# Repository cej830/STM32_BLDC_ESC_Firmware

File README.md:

# STM32 Sensorless BLDC ESC

STM32F103C8 기반 센서리스 BLDC ESC. 회로·4-layer PCB 설계 및 펌웨어 구현을 수행하고
12V에서 A2212/13T 1000kV 모터의 무부하 구동을 확인했다.

## Highlights
- 4층 기판 3상 ESC 하드웨어 설계부터 회로도 작성, 조립 및 보드 브링업 수행
- 오픈루프 기동 및 BEMF(역기전력) 클로즈드 루프 정류를 적용한 센서리스 6스텝 제어 구현
- ADC 기반 제로 크로싱 검출 방식 적용, 고듀티 구간에서는 외부 비교기 및 TIM2 Input Capture 로 전환
- 12V 환경에서 A2212/13T 1000kV 모터를 무부하 조건에서 CCR 1750/1800까지 구동 시험 완료

## Hardware

- **MCU:** STM32F103C8T6
- **Gate driver / MOSFET:** DRV8300 / IRFH7440 × 6
- **PCB:** 4-layer, 1.6mm
- **Power:** 12V→5V Buck, USB 5V와 diode ORing, 3.3V LDO
- **BEMF sensing:** 상전압 ADC 입력 및 TLV3202 외부 비교기
- **Current sensing:** 10mΩ 로우사이드 션트 및 INA180A3 × 3
- **Interface:** USB 2.0 FullSpeed, UART, LED, 버튼, 가변저항, 테스트 포인트

회로,BOM 작성, PCB 부품 배치 및 배선, 보드 bring-up을 직접 수행했다. 부품 실장은 SMT 조립을 외주하였다.

### 3D Board View

### Schematic

### PCB Layout — Front / Back

### Assembled Board

실물 수정: USB 풀업 저항 직결, Vcom 비교기 입력 커패시터 제거.

[하드웨어 구성 상세](docs/portfolio/architecture.md)

## Firmware

C, STM32 HAL 및 레지스터 제어로 구현한 인터럽트 기반 펌웨어. Open-loop 기동 후 BEMF 기반 six-step 정류로 전환

듀티 구간에 따라 ADC 기반 swBEMF·선형보간 또는 외부 비교기 출력의 TIM2 input capture로 ZC를 검출한다. TIM3로 다음 정류를 예약하고 TIM1 상보 PWM 출력을 갱신한다. 운전 데이터는 USB CDC로 전송한다.

[제어 코드](Core/Src/layer_1_Algorithm/algorithm_BLDC_Control.c) · [주변장치·정류표 상세](docs/portfolio/architecture.md)

## Testing

### Setup

- **Motor:** A2212/13T 1000kV
- **Supply:** 12V DC power supply
- **Load:** 무부하
- **Input:** 가변저항 ADC 값으로 CCR 조절
- **Observation:** 오실로스코프, USB CDC 모니터

### Results

#### Motor Operation

<div align="center">
  
  <p>
    <a href="https://youtu.be/g03CNRUJoPk">▶ YouTube에서 동작 영상 보기</a>
  </p>
</div>

| 항목 | 관찰 결과 |
| --- | --- |
| 속도 조절 | 노브 입력에 따른 CCR 및 회전 속도 변화 확인 |
| 최대 시험 설정 | ARR=1800, CCR=1750 — 설정 비율 약 97.2% |

#### PC Monitor

USB CDC 수신 데이터 표시 및 CSV 저장. RPM은 추정값이며, 션트 전류 환산값의 정확도는 미검증.

#### Oscilloscope

CH1: 스텝 GPIO · CH2: 플로팅 상 · CH3: Vcom · CH4: 비교기 출력.

각 행은 왼쪽 Step 1, 오른쪽 Step 2 파형으로 구성.

**저듀티 CCR 220**

**중듀티 CCR 700**

**고듀티 CCR 1400**

## Board Changes & Limitations

- **USB pull-up:** 제어 MOSFET 풋프린트 오류를 배선으로 수정하고 PA12 LOW 초기화 적용. 이후 USB 인식 회복 확인.
- **Comparator:** Vcom 커패시터 제거 후 고듀티에서 다중 에지 감소 관찰 및 input capture 경로 활용.
- **Current / Operation:** 모터 발열 및 특정 CCR에서 구동음 발생. 전류 측정 정확도, 부하 기동, 장시간 운전, 효율·정격·보호 성능은 미검증.

[개발 과정 및 디버깅 기록](docs/portfolio/development-story.md)

## Repository

| 위치 | 내용 |
| --- | --- |
| [Core](Core) | Driver / Algorithm / Service / Utility 및 헤더 |
| [Drivers](Drivers), [Middlewares](Middlewares), [USB_DEVICE](USB_DEVICE) | HAL·CMSIS, 미들웨어, USB 구성 |
| [CubeMX .ioc](BLDC_ESC_Based_On_HW_Test.ioc) | MCU 설정 |
| [ESC_Monitor](ESC_Monitor) | 수신·표시·CSV 저장 프로그램 |
| [Architecture](docs/portfolio/architecture.md) | HW/FW 구조와 제어 흐름 |

**개발 환경:** STM32CubeIDE, KiCad

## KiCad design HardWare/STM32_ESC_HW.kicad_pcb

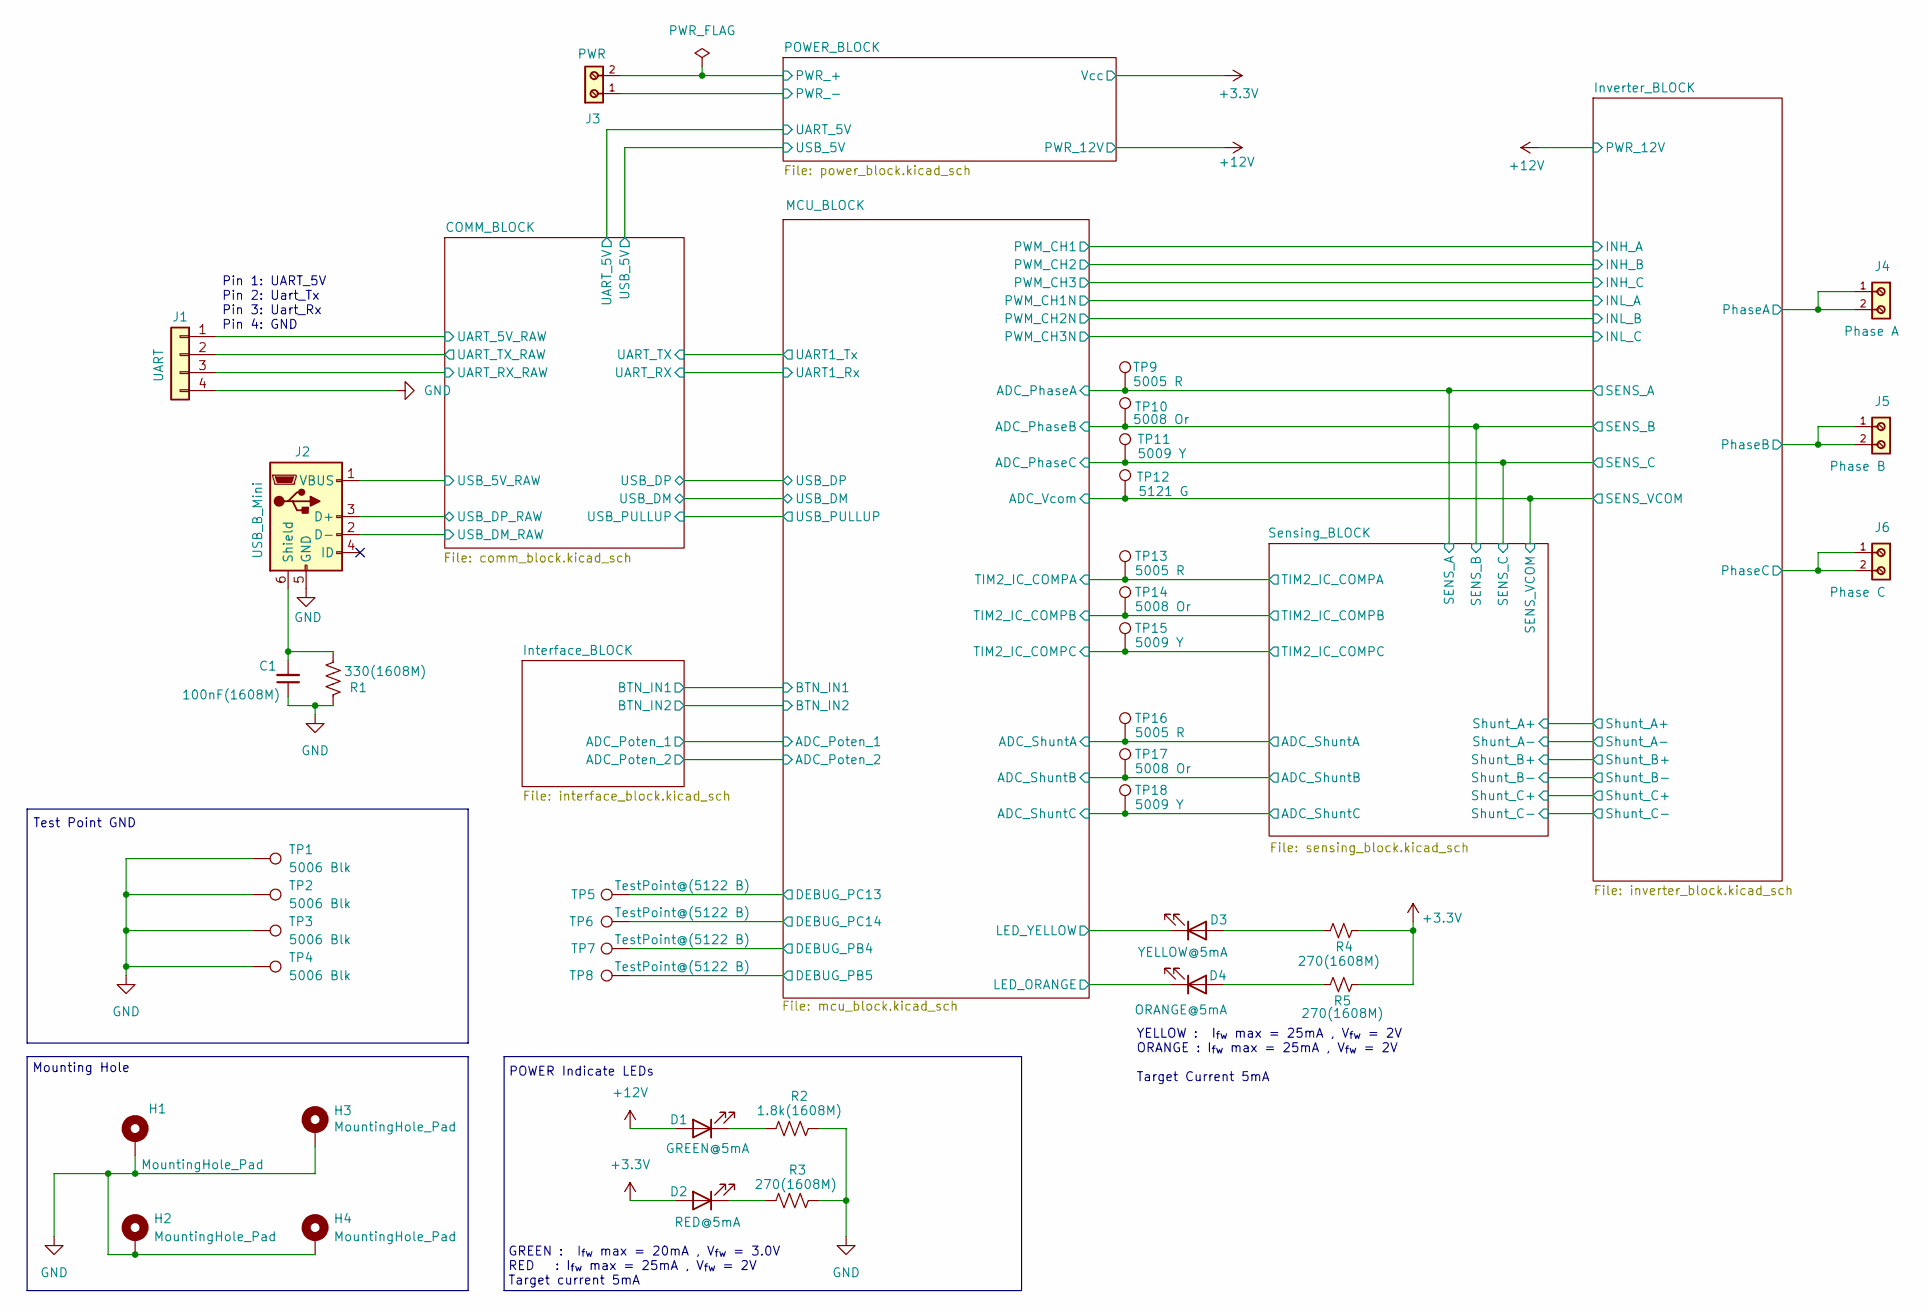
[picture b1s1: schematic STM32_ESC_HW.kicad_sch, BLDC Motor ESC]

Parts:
C1: 100nF(1608M); C_0603_1608Metric; Part number GRM188R71H104KA93D
D1: GREEN@5mA; LED_0603_1608Metric; Part number NCD0603G1
D2: RED@5mA; LED_0603_1608Metric; Part number NCD0603R1
D3: YELLOW@5mA; LED_0603_1608Metric; Part number NCD0603C1
D4: ORANGE@5mA; LED_0603_1608Metric; Part number NCD0603O1
H1, H2, H3, H4: MountingHole_Pad; MountingHole_3.2mm_M3_DIN965_Pad
J1: UART; PinHeader_1x04_P2.54mm_Vertical; Part number 254PZ-1x4P-V
J2: USB_B_Mini; USB_Mini B 920-462A2021S10101; Part number 920-462A2021S10101
J3: PWR; TERM BLK 2POS SIDE ENTRY 5MM PCB; Part number 691137710002
J4: Phase A; TERM BLK 2POS SIDE ENTRY 5MM PCB; Part number 691137710002
J5: Phase B; TERM BLK 2POS SIDE ENTRY 5MM PCB; Part number 691137710002
J6: Phase C; TERM BLK 2POS SIDE ENTRY 5MM PCB; Part number 691137710002
R1: 330(1608M); R_0603_1608Metric; Part number 0603WAF3300T5E
R2: 1.8k(1608M); R_0603_1608Metric; Part number 0603WAJ0182T5E
R3, R4, R5: 270(1608M); R_0603_1608Metric; Part number 0603WAJ0271T5E
TP1, TP2, TP3, TP4: 5006 Blk; TestPoint_Keystone_5005-5009_Compact; Part number RH-5006
TP5, TP6, TP7, TP8: TestPoint@(5122 B); TestPoint_Keystone_5005-5009_Compact; Part number RH-5122
TP9, TP13, TP16: 5005 R; TestPoint_Keystone_5005-5009_Compact; Part number RH-5005
TP10: 5008 Or; TestPoint_Keystone_5005-5009_Compact; Part number RH-5008
TP11: 5009 Y; TestPoint_Keystone_5005-5009_Compact; Part number RH-5009
TP12: 5121 G; TestPoint_Keystone_5005-5009_Compact; Part number RH-5121
TP14, TP17: 5008 Or; TestPoint_Keystone_5005-5009_Compact; Part number RH-5005
TP15, TP18: 5009 Y; TestPoint_Keystone_5005-5009_Compact; Part number RH-5005

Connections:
+3.3V: D2.2 (A), R4.2, R5.2; also elsewhere on the board
+12V: D1.2 (A); also elsewhere on the board
/COMM_BLOCK/UART_RX_RAW: J1.3; also elsewhere on the board
/COMM_BLOCK/UART_TX_RAW: J1.2; also elsewhere on the board
/COMM_BLOCK/USB_D_N: J2.2 (D-); also elsewhere on the board
/COMM_BLOCK/USB_D_P: J2.3 (D+); also elsewhere on the board
/Inverter_BLOCK/PhaseA: J4.1, J4.2; also elsewhere on the board
/Inverter_BLOCK/PhaseB: J5.1, J5.2; also elsewhere on the board
/Inverter_BLOCK/PhaseC: J6.1, J6.2; also elsewhere on the board
/Inverter_BLOCK/SENS_A: TP9.1; also elsewhere on the board
/Inverter_BLOCK/SENS_B: TP10.1; also elsewhere on the board
/Inverter_BLOCK/SENS_C: TP11.1; also elsewhere on the board
/Inverter_BLOCK/SENS_VCOM: TP12.1; also elsewhere on the board
/MCU_BLOCK/ADC_ShuntA: TP16.1; also elsewhere on the board
/MCU_BLOCK/ADC_ShuntB: TP17.1; also elsewhere on the board
/MCU_BLOCK/ADC_ShuntC: TP18.1; also elsewhere on the board
/MCU_BLOCK/DEBUG_PB4: TP7.1; also elsewhere on the board
/MCU_BLOCK/DEBUG_PB5: TP8.1; also elsewhere on the board
/MCU_BLOCK/DEBUG_PC13: TP5.1; also elsewhere on the board
/MCU_BLOCK/DEBUG_PC14: TP6.1; also elsewhere on the board
/MCU_BLOCK/LED_ORANGE: D4.1 (K); also elsewhere on the board
/MCU_BLOCK/LED_YELLOW: D3.1 (K); also elsewhere on the board
/MCU_BLOCK/TIM2_IC_COMPA: TP13.1; also elsewhere on the board
/MCU_BLOCK/TIM2_IC_COMPB: TP14.1; also elsewhere on the board
/MCU_BLOCK/TIM2_IC_COMPC: TP15.1; also elsewhere on the board
/POWER_BLOCK/PWR_+: J3.2; also elsewhere on the board
/POWER_BLOCK/UART_5V: J1.1; also elsewhere on the board
/POWER_BLOCK/USB_5V: J2.1 (VBUS); also elsewhere on the board
GND: C1.1, H1.1, H2.1, H3.1, H4.1, J1.4, J2.5 (GND), J3.1, R1.1, R2.2, R3.2, TP1.1, TP2.1, TP3.1, TP4.1; also elsewhere on the board
unnamed: D1.1 (K), R2.1
unnamed: D2.1 (K), R3.1
unnamed: D3.2 (A), R4.1
unnamed: D4.2 (A), R5.1
unnamed: C1.2, J2.6 (Shield), R1.2

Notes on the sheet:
YELLOW : I_{fw} max = 25mA , V_{fw} = 2V ORANGE : I_{fw} max = 25mA , V_{fw} = 2V Target Current 5mA
GREEN : I_{fw} max = 20mA , V_{fw} = 3.0V RED : I_{fw} max = 25mA , V_{fw} = 2V Target current 5mA
Mounting Hole
Test Point GND
POWER Indicate LEDs
Pin 1: UART_5V Pin 2: Uart_Tx Pin 3: Uart_Rx Pin 4: GND

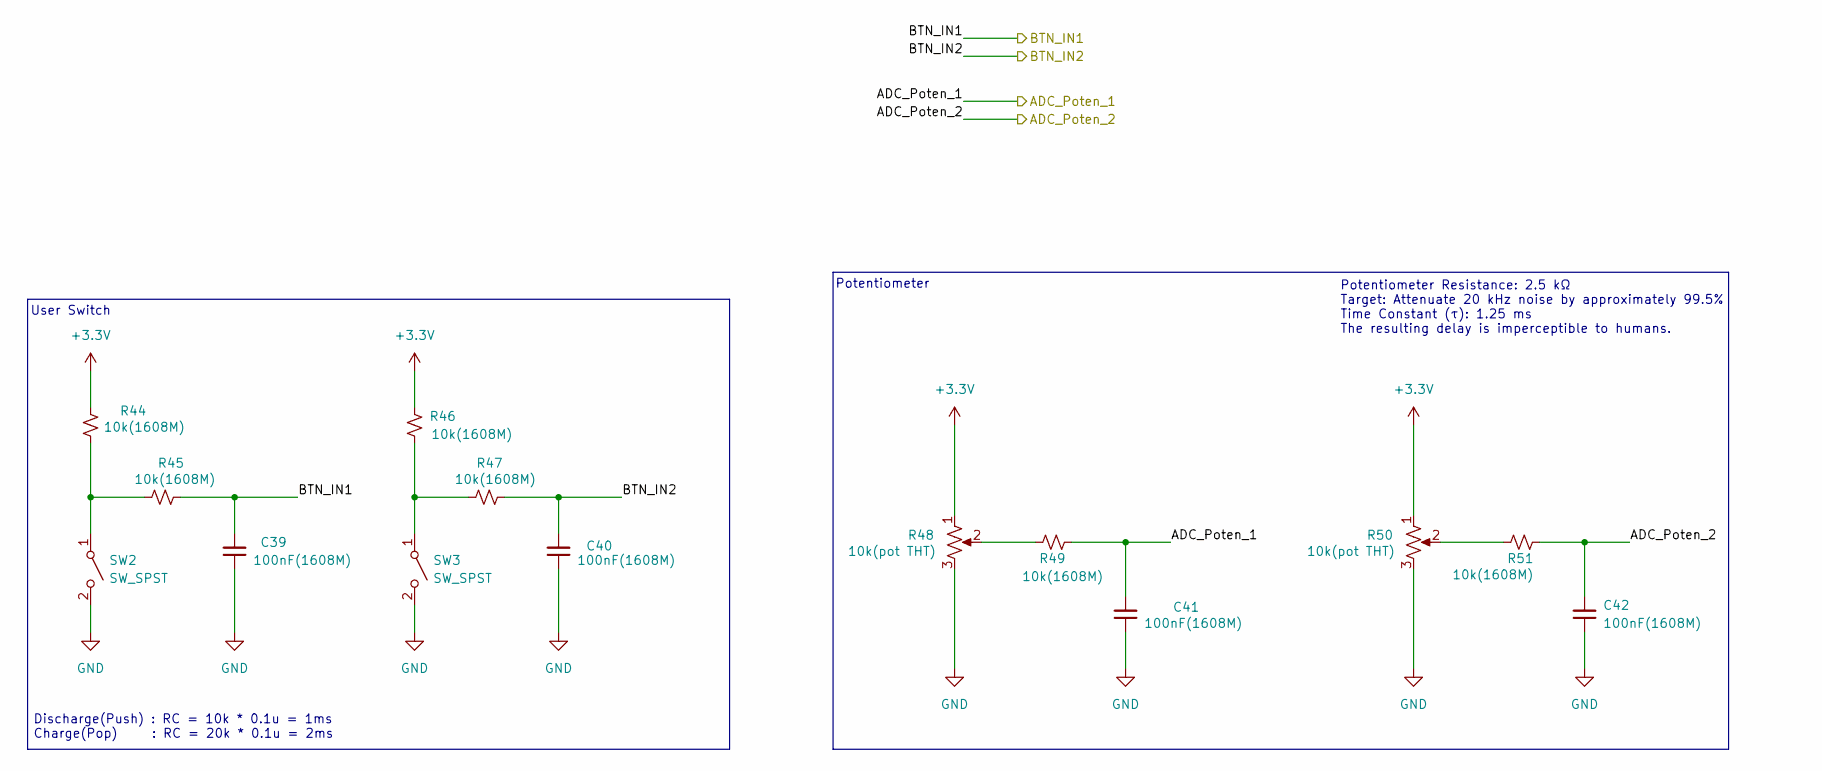
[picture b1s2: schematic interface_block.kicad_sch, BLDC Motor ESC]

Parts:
C39, C40, C41, C42: 100nF(1608M); C_0603_1608Metric; Part number GRM188R71H104KA93D
R44, R45, R46, R47, R49, R51: 10k(1608M); R_0603_1608Metric; Part number 0603WAF1002T5E
R48, R50: 10k(pot THT); Potentiometer_Alps_RK09K_Single_Vertical; Part number RK09K1130AAU
SW2, SW3: SW_SPST; Button_Switch_SMD SW_Push_1P1T SMD-4P,6x6mm; Part number UK-B0228-G5-160-JZ

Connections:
+3.3V: R44.1, R46.1, R48.1, R50.1; also elsewhere on the board
/Interface_BLOCK/ADC_Poten_1: C41.2, R49.2; also elsewhere on the board
/Interface_BLOCK/ADC_Poten_2: C42.2, R51.2; also elsewhere on the board
/Interface_BLOCK/BTN_IN1: C39.2, R45.1; also elsewhere on the board
/Interface_BLOCK/BTN_IN2: C40.2, R47.1; also elsewhere on the board
GND: C39.1, C40.1, C41.1, C42.1, R48.3, R50.3, SW2.2 (B), SW3.2 (B); also elsewhere on the board
unnamed: R48.2, R49.1
unnamed: R50.2, R51.1
unnamed: R44.2, R45.2, SW2.1 (A)
unnamed: R46.2, R47.2, SW3.1 (A)

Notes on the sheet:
Potentiometer
User Switch
Discharge(Push) : RC = 10k * 0.1u = 1ms Charge(Pop) : RC = 20k * 0.1u = 2ms
Potentiometer Resistance: 2.5 kΩ Target: Attenuate 20 kHz noise by approximately 99.5% Time Constant (τ): 1.25 ms The resulting delay is imperceptible to humans.

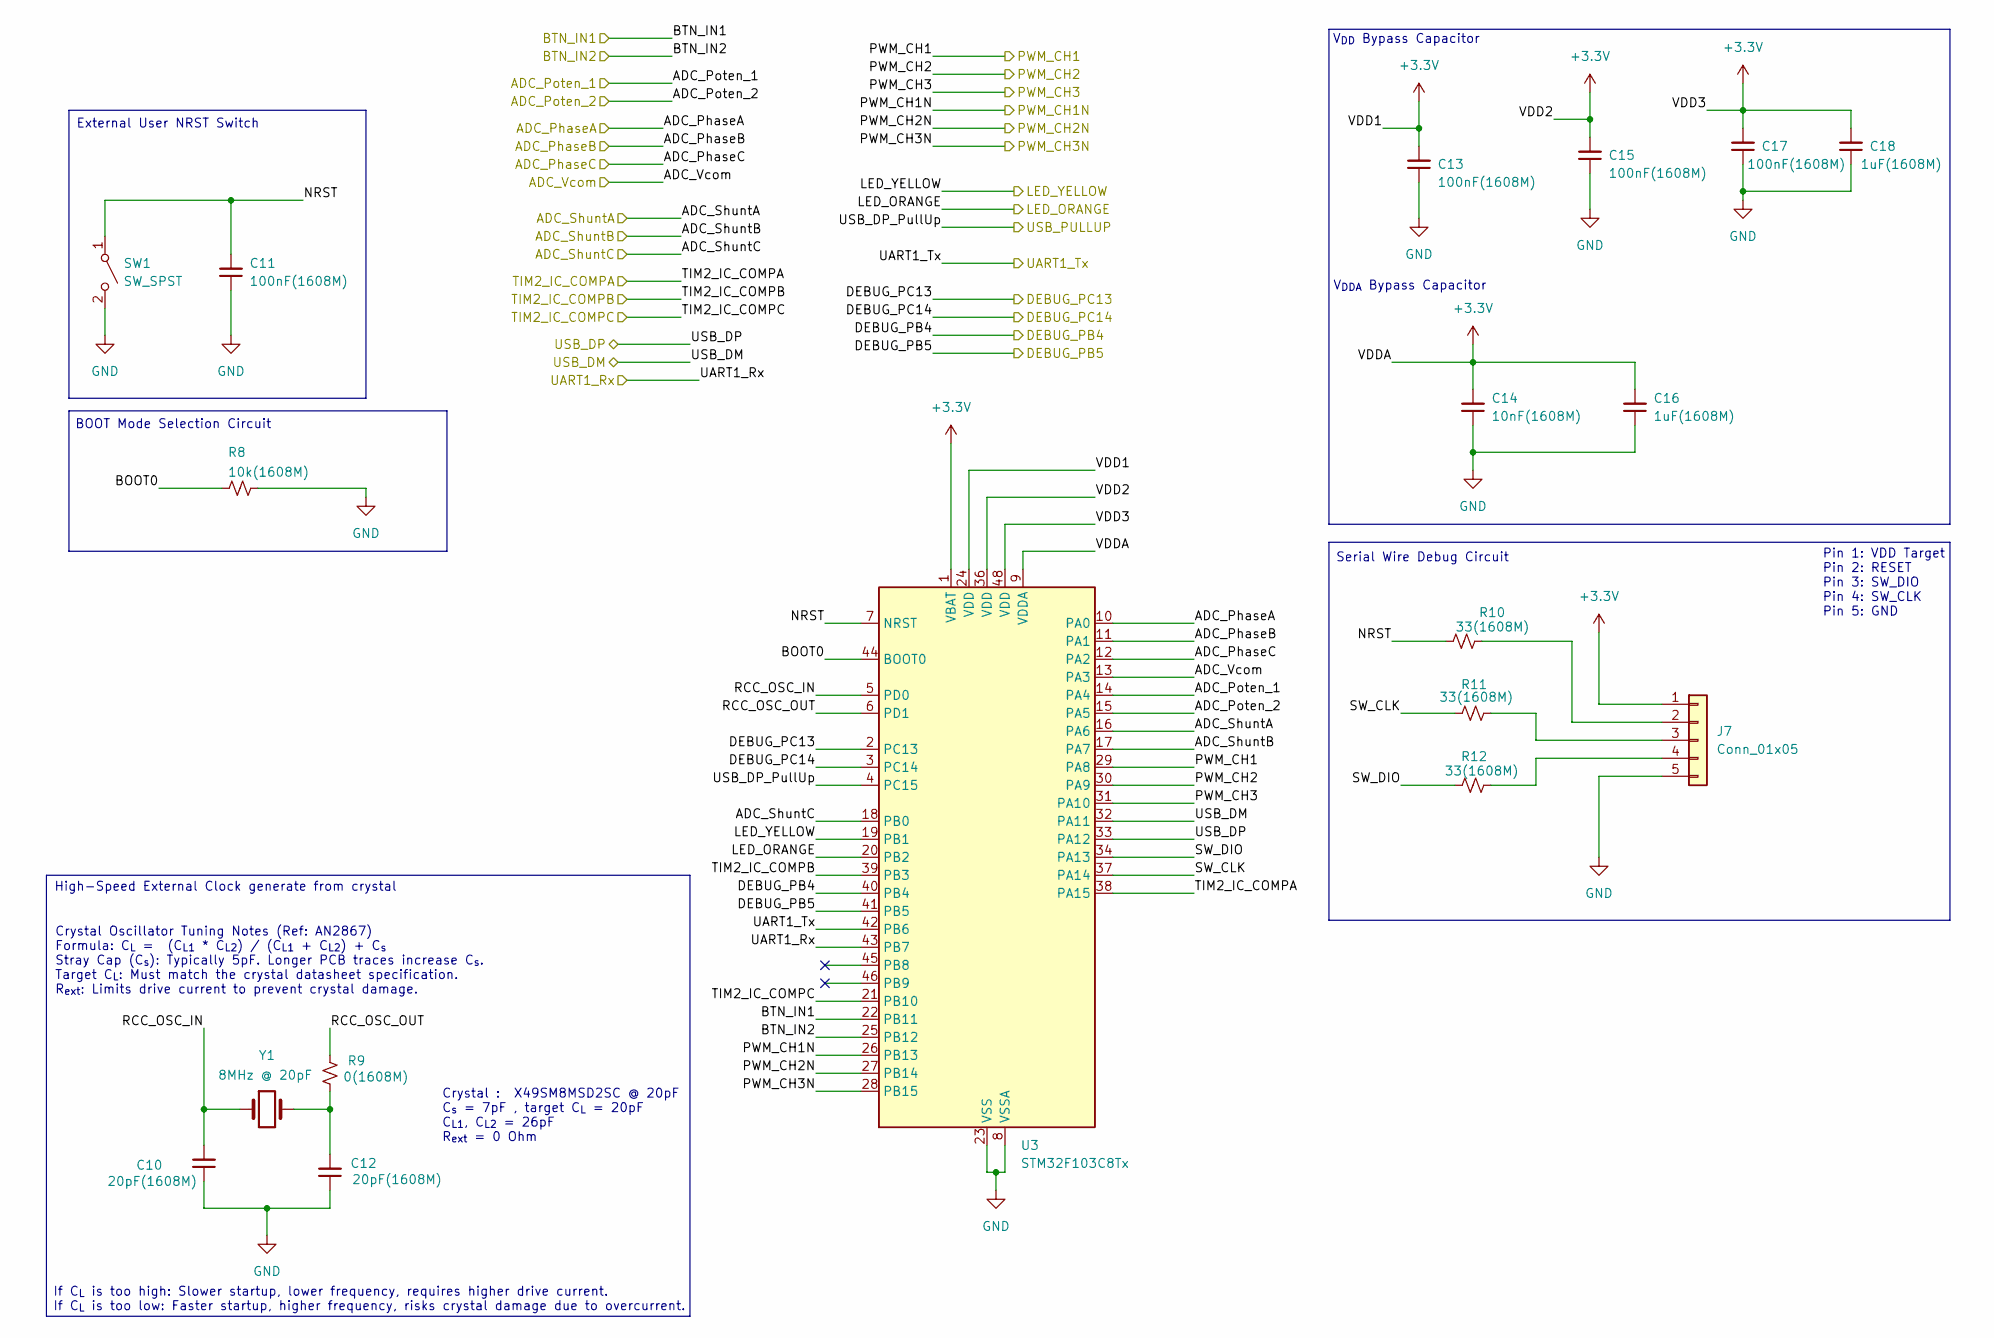
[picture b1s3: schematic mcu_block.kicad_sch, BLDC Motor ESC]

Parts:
C10, C12: 20pF(1608M); C_0603_1608Metric; Part number CL10C200JB8NNNC
C11, C13, C15, C17: 100nF(1608M); C_0603_1608Metric; Part number GRM188R71H104KA93D
C14: 10nF(1608M); C_0603_1608Metric; Part number CL10B103KB8NNNC
C16, C18: 1uF(1608M); C_0603_1608Metric; Part number CL10A105KA8NNNC
J7: Conn_01x05; PinHeader_1x05_P2.54mm_Vertical; Part number 2.54-1*5
R8: 10k(1608M); R_0603_1608Metric; Part number 0603WAF1002T5E
R9: 0(1608M); R_0603_1608Metric; Part number 0603WAF0000T5E
R10, R11, R12: 33(1608M); R_0603_1608Metric; Part number 0603WAF330JT5E
SW1: SW_SPST; Button_Switch_SMD SW_Push_1P1T SMD-4P,6x6mm; Part number UK-B0228-G5-160-JZ
U3: STM32F103C8Tx; LQFP-48_7x7mm_P0.5mm; Part number STM32F103C8T6
Y1: 8MHz @ 20pF; Crystal_SMD_HC49-SD; Partnum# C12674

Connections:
+3.3V: C13.2, C14.2, C15.2, C16.2, C17.2, C18.2, J7.1, U3.1 (VBAT), U3.9 (VDDA), U3.24 (VDD), U3.36 (VDD), U3.48 (VDD); also elsewhere on the board
/COMM_BLOCK/USB_+: U3.33 (PA12); also elsewhere on the board
/COMM_BLOCK/USB_-: U3.32 (PA11); also elsewhere on the board
/Interface_BLOCK/ADC_Poten_1: U3.14 (PA4); also elsewhere on the board
/Interface_BLOCK/ADC_Poten_2: U3.15 (PA5); also elsewhere on the board
/Interface_BLOCK/BTN_IN1: U3.22 (PB11); also elsewhere on the board
/Interface_BLOCK/BTN_IN2: U3.25 (PB12); also elsewhere on the board
/Inverter_BLOCK/SENS_A: U3.10 (PA0); also elsewhere on the board
/Inverter_BLOCK/SENS_B: U3.11 (PA1); also elsewhere on the board
/Inverter_BLOCK/SENS_C: U3.12 (PA2); also elsewhere on the board
/Inverter_BLOCK/SENS_VCOM: U3.13 (PA3); also elsewhere on the board
/MCU_BLOCK/ADC_ShuntA: U3.16 (PA6); also elsewhere on the board
/MCU_BLOCK/ADC_ShuntB: U3.17 (PA7); also elsewhere on the board
/MCU_BLOCK/ADC_ShuntC: U3.18 (PB0); also elsewhere on the board
/MCU_BLOCK/BOOT0: R8.2, U3.44 (BOOT0)
/MCU_BLOCK/DEBUG_PB4: U3.40 (PB4); also elsewhere on the board
/MCU_BLOCK/DEBUG_PB5: U3.41 (PB5); also elsewhere on the board
/MCU_BLOCK/DEBUG_PC13: U3.2 (PC13); also elsewhere on the board
/MCU_BLOCK/DEBUG_PC14: U3.3 (PC14); also elsewhere on the board
/MCU_BLOCK/LED_ORANGE: U3.20 (PB2); also elsewhere on the board
/MCU_BLOCK/LED_YELLOW: U3.19 (PB1); also elsewhere on the board
/MCU_BLOCK/NRST: C11.2, R10.2, SW1.1 (A), U3.7 (NRST)
/MCU_BLOCK/PWM_CH1: U3.29 (PA8); also elsewhere on the board
/MCU_BLOCK/PWM_CH1N: U3.26 (PB13); also elsewhere on the board
/MCU_BLOCK/PWM_CH2: U3.30 (PA9); also elsewhere on the board
/MCU_BLOCK/PWM_CH2N: U3.27 (PB14); also elsewhere on the board
/MCU_BLOCK/PWM_CH3: U3.31 (PA10); also elsewhere on the board
/MCU_BLOCK/PWM_CH3N: U3.28 (PB15); also elsewhere on the board
/MCU_BLOCK/RCC_OSC_IN: C10.2, U3.5 (PD0), Y1.1
/MCU_BLOCK/RCC_OSC_OUT: R9.2, U3.6 (PD1)
/MCU_BLOCK/SW_CLK: R11.2, U3.37 (PA14)
/MCU_BLOCK/SW_DIO: R12.2, U3.34 (PA13)
/MCU_BLOCK/TIM2_IC_COMPA: U3.38 (PA15); also elsewhere on the board
/MCU_BLOCK/TIM2_IC_COMPB: U3.39 (PB3); also elsewhere on the board
/MCU_BLOCK/TIM2_IC_COMPC: U3.21 (PB10); also elsewhere on the board
/MCU_BLOCK/UART1_Rx: U3.43 (PB7); also elsewhere on the board
/MCU_BLOCK/UART1_Tx: U3.42 (PB6); also elsewhere on the board
/MCU_BLOCK/USB_DP_PullUp: U3.4 (PC15); also elsewhere on the board
GND: C10.1, C11.1, C12.1, C13.1, C14.1, C15.1, C16.1, C17.1, C18.1, J7.5, R8.1, SW1.2 (B), U3.8 (VSSA), U3.23 (VSS), U3.35 (VSS), U3.47 (VSS); also elsewhere on the board
unnamed: C12.2, R9.1, Y1.2
unnamed: J7.2, R10.1
unnamed: J7.3, R11.1
unnamed: J7.4, R12.1

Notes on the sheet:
External User NRST Switch
Serial Wire Debug Circuit
High-Speed External Clock generate from crystal
Pin 1: VDD Target Pin 2: RESET Pin 3: SW_DIO Pin 4: SW_CLK Pin 5: GND
Crystal : X49SM8MSD2SC @ 20pF C_{s} = 7pF , target C_{L} = 20pF C_{L1}, C_{L2} = 26pF R_{ext} = 0 Ohm
V_{DD} Bypass Capacitor
V_{DDA} Bypass Capacitor
Crystal Oscillator Tuning Notes (Ref: AN2867) Formula: C_{L} = (C_{L1} * C_{L2}) / (C_{L1} + C_{L2}) + C_{s} Stray Cap (C_{s}): Typically 5pF. Longer PCB traces increase C_{s}. Target C_{L}: Must match the crystal datasheet specification. R_{ext}: Limits drive current to prevent crystal damage.
If C_{L} is too high: Slower startup, lower frequency, requires higher drive current. If C_{L} is too low: Faster startup, higher frequency, risks crystal damage due to overcurrent.
BOOT Mode Selection Circuit

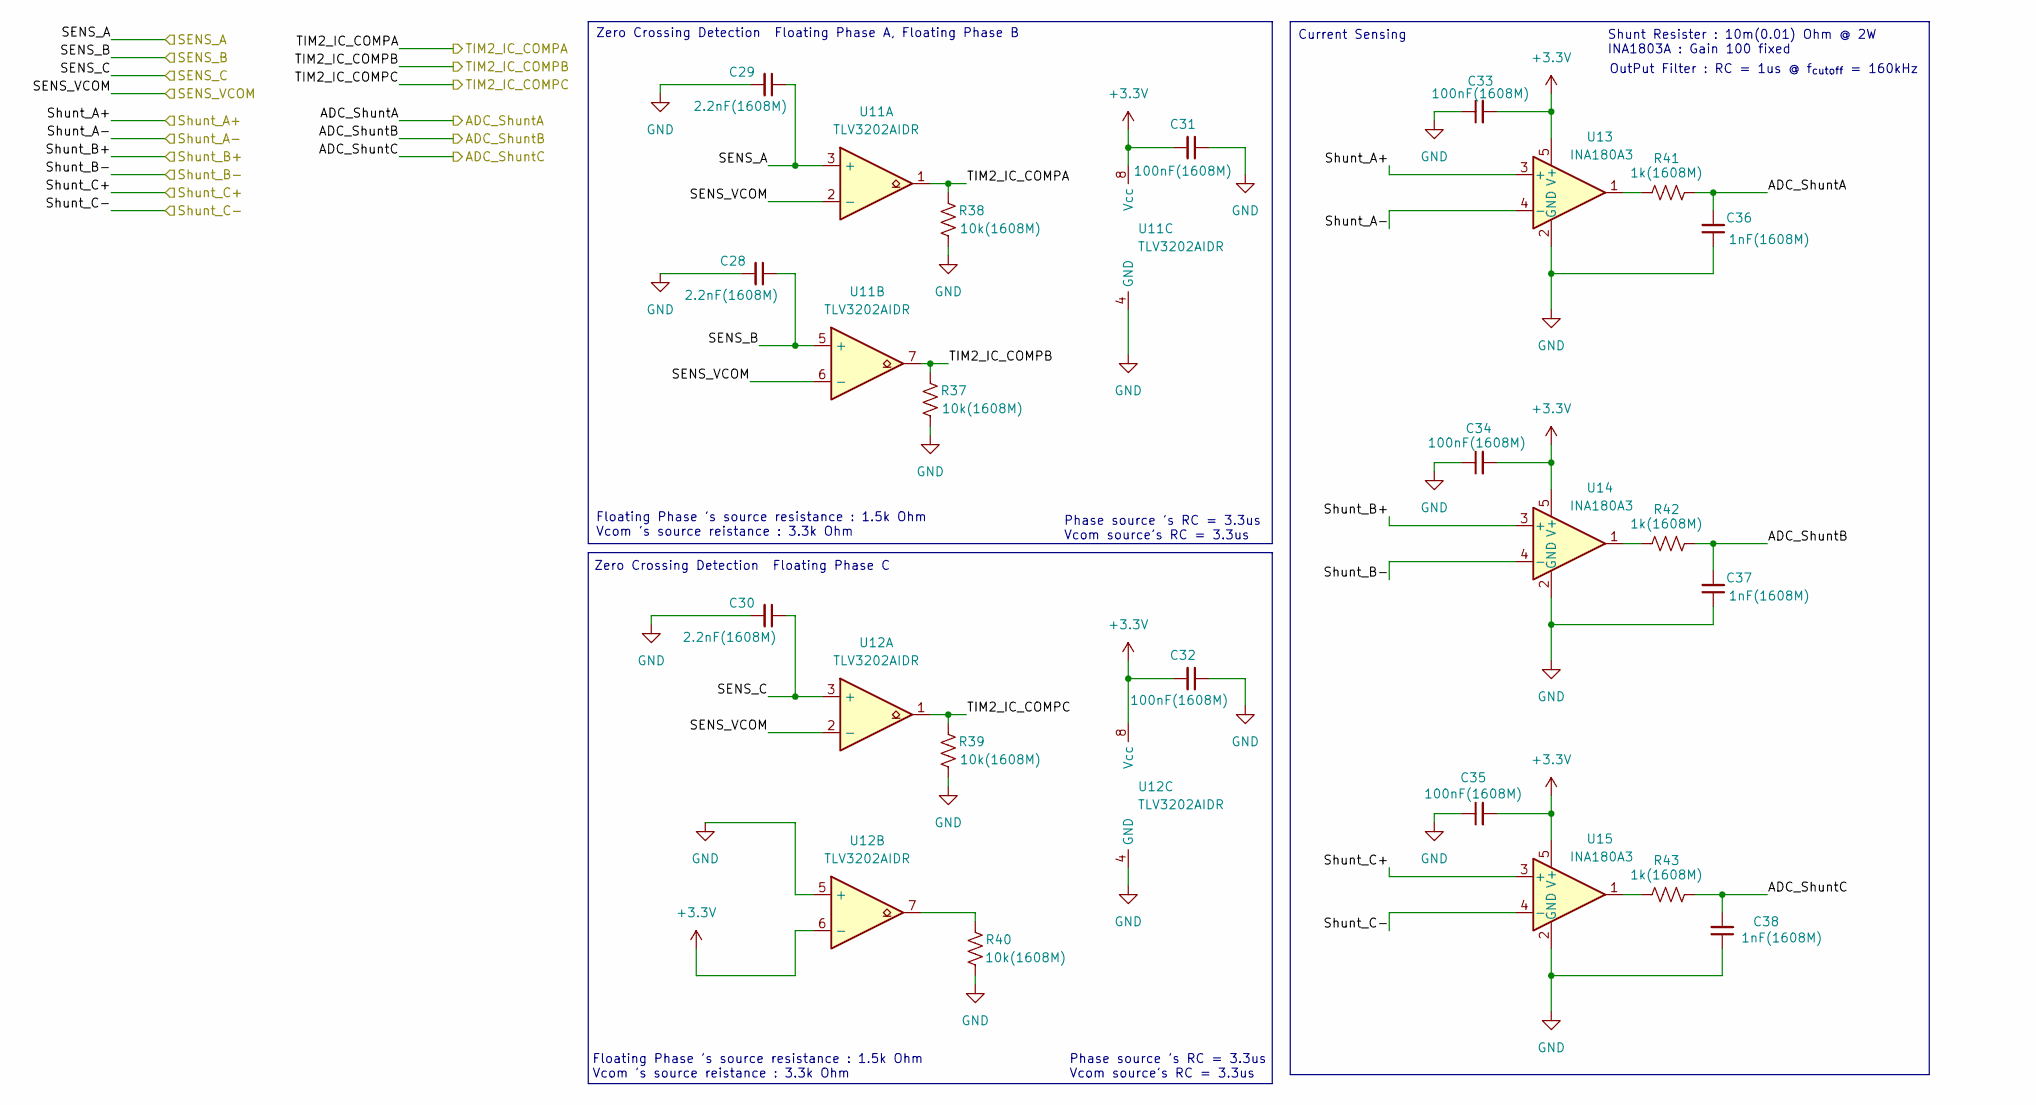
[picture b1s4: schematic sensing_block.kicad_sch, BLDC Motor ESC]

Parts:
C28, C29, C30: 2.2nF(1608M); C_0603_1608Metric; Part number CL10B222KB8NNNC
C31, C32, C33, C34, C35: 100nF(1608M); C_0603_1608Metric; Part number GRM188R71H104KA93D
C36, C37, C38: 1nF(1608M); C_0603_1608Metric; Part number CL10B102KB8NNNC
R37, R38, R39, R40: 10k(1608M); R_0603_1608Metric; Part number 0603WAF1002T5E
R41, R42, R43: 1k(1608M); R_0603_1608Metric; Part number 0603WAF1001T5E
U11, U12: TLV3202AIDR; SOIC-8_3.9x4.9mm_P1.27mm; Part number TLV3202AIDR
U13, U14, U15: INA180A3; SOT-23-5; Part number INA180A3IDBVR

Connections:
+3.3V: C31.2, C32.2, C33.2, C34.2, C35.2, U11.8 (Vcc), U12.6 (-), U12.8 (Vcc), U13.5 (V+), U14.5 (V+), U15.5 (V+); also elsewhere on the board
/Inverter_BLOCK/SENS_A: C29.1, U11.3 (+); also elsewhere on the board
/Inverter_BLOCK/SENS_B: C28.1, U11.5 (+); also elsewhere on the board
/Inverter_BLOCK/SENS_C: C30.1, U12.3 (+); also elsewhere on the board
/Inverter_BLOCK/SENS_VCOM: U11.2 (-), U11.6 (-), U12.2 (-); also elsewhere on the board
/Inverter_BLOCK/Shunt_A+: U13.3 (+); also elsewhere on the board
/Inverter_BLOCK/Shunt_B+: U14.3 (+); also elsewhere on the board
/Inverter_BLOCK/Shunt_C+: U15.3 (+); also elsewhere on the board
/MCU_BLOCK/ADC_ShuntA: C36.2, R41.2; also elsewhere on the board
/MCU_BLOCK/ADC_ShuntB: C37.2, R42.2; also elsewhere on the board
/MCU_BLOCK/ADC_ShuntC: C38.2, R43.2; also elsewhere on the board
/MCU_BLOCK/TIM2_IC_COMPA: R38.1, U11.1; also elsewhere on the board
/MCU_BLOCK/TIM2_IC_COMPB: R37.1, U11.7; also elsewhere on the board
/MCU_BLOCK/TIM2_IC_COMPC: R39.1, U12.1; also elsewhere on the board
GND: C28.2, C29.2, C30.2, C31.1, C32.1, C33.1, C34.1, C35.1, C36.1, C37.1, C38.1, R37.2, R38.2, R39.2, R40.2, U11.4 (GND), U12.4 (GND), U12.5 (+), U13.2 (GND), U13.4 (-), U14.2 (GND), U14.4 (-), U15.2 (GND), U15.4 (-); also elsewhere on the board
unnamed: R40.1, U12.7
unnamed: R41.1, U13.1
unnamed: R42.1, U14.1
unnamed: R43.1, U15.1

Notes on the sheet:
Shunt Resister : 10m(0.01) Ohm @ 2W INA1803A : Gain 100 fixed
Zero Crossing Detection Floating Phase A, Floating Phase B
Phase source 's RC = 3.3us Vcom source's RC = 3.3us
Zero Crossing Detection Floating Phase C
Floating Phase 's source resistance : 1.5k Ohm Vcom 's source reistance : 3.3k Ohm
Current Sensing
OutPut Filter : RC = 1us @ f_{cutoff} = 160kHz

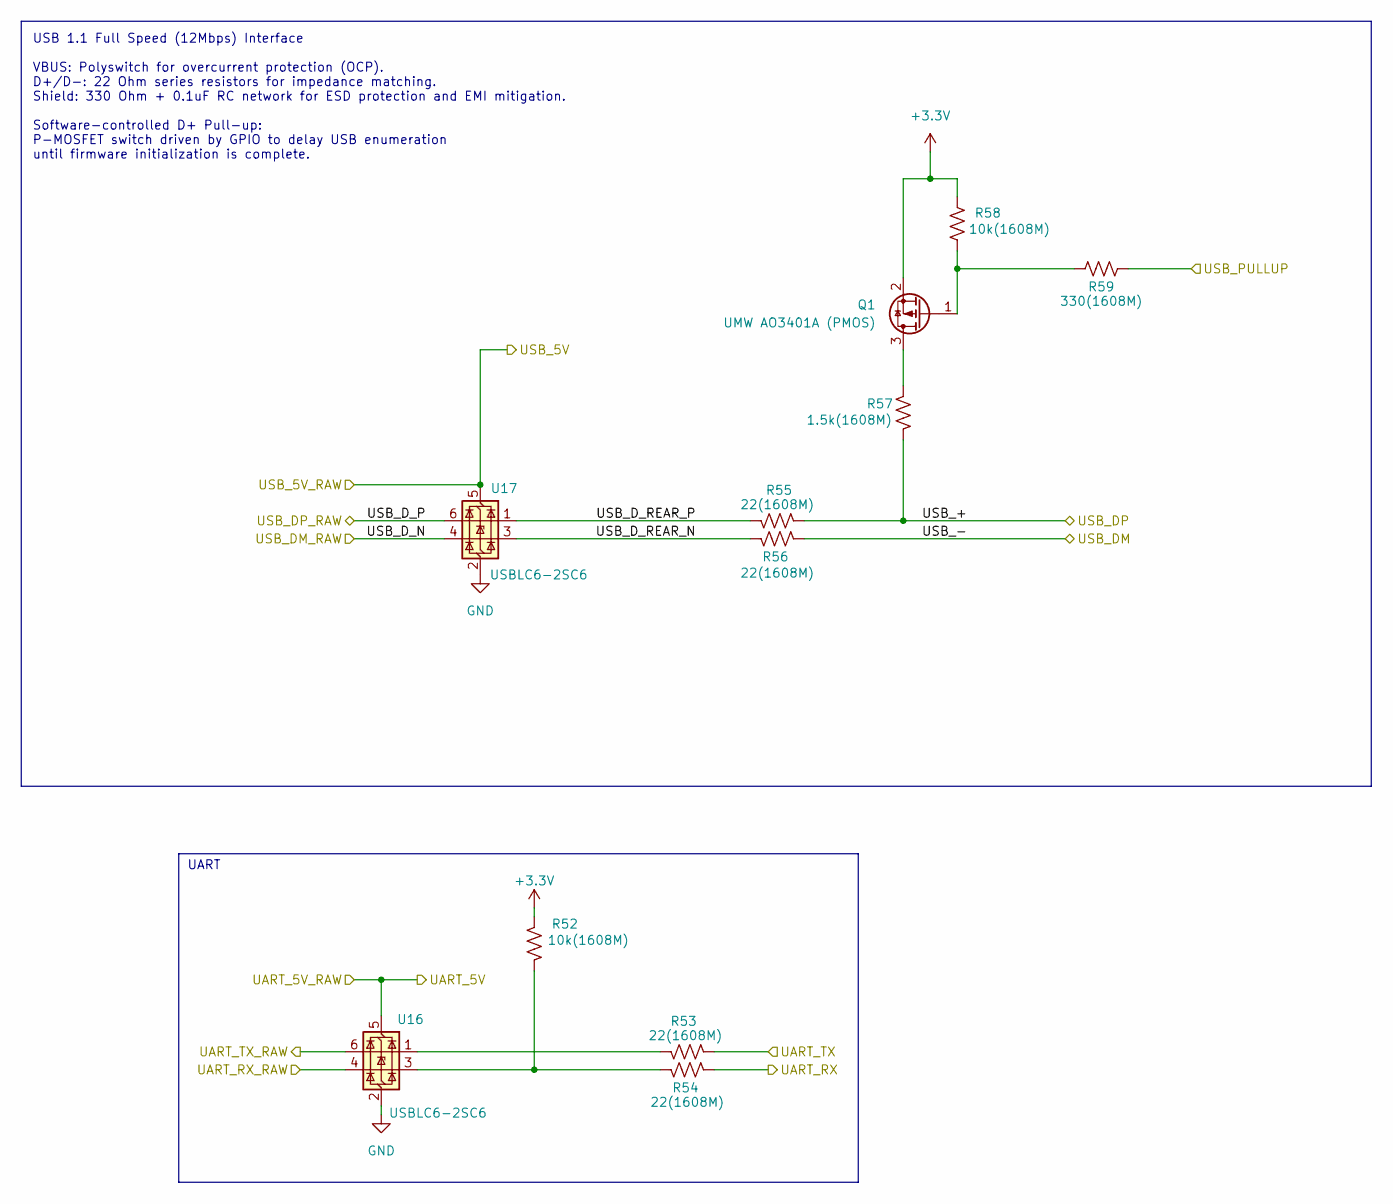
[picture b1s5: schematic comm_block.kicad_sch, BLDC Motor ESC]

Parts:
Q1: UMW AO3401A (PMOS); SOT-23; Part number AO3401A
R52, R58: 10k(1608M); R_0603_1608Metric; Part number 0603WAF1002T5E
R53, R54, R55, R56: 22(1608M); R_0603_1608Metric; Part number 0603WAF220JT5E
R57: 1.5k(1608M); R_0603_1608Metric; Part number 0603WAF1501T5E
R59: 330(1608M); R_0603_1608Metric; Part number 0603WAF3300T5E
U16, U17: USBLC6-2SC6; SOT-23-6; Part number USBLC6-2SC6

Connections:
+3.3V: Q1.2 (S), R52.1, R58.1; also elsewhere on the board
/COMM_BLOCK/UART_RX_RAW: U16.4 (I/O2); also elsewhere on the board
/COMM_BLOCK/UART_TX_RAW: U16.6 (I/O1); also elsewhere on the board
/COMM_BLOCK/USB_+: R55.1, R57.2; also elsewhere on the board
/COMM_BLOCK/USB_-: R56.1; also elsewhere on the board
/COMM_BLOCK/USB_D_N: U17.4 (I/O2); also elsewhere on the board
/COMM_BLOCK/USB_D_P: U17.6 (I/O1); also elsewhere on the board
/COMM_BLOCK/USB_D_REAR_N: R56.2, U17.3 (I/O2)
/COMM_BLOCK/USB_D_REAR_P: R55.2, U17.1 (I/O1)
/MCU_BLOCK/UART1_Rx: R54.1; also elsewhere on the board
/MCU_BLOCK/UART1_Tx: R53.1; also elsewhere on the board
/MCU_BLOCK/USB_DP_PullUp: R59.1; also elsewhere on the board
/POWER_BLOCK/UART_5V: U16.5 (VBUS); also elsewhere on the board
/POWER_BLOCK/USB_5V: U17.5 (VBUS); also elsewhere on the board
GND: U16.2 (GND), U17.2 (GND); also elsewhere on the board
unnamed: Q1.3 (D), R57.1
unnamed: Q1.1 (G), R58.2, R59.2
unnamed: R52.2, R54.2, U16.3 (I/O2)
unnamed: R53.2, U16.1 (I/O1)

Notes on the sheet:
USB 1.1 Full Speed (12Mbps) Interface VBUS: Polyswitch for overcurrent protection (OCP). D+/D-: 22 Ohm series resistors for impedance matching. Shield: 330 Ohm + 0.1uF RC network for ESD protection and EMI mitigation. Software-controlled D+ Pull-up: P-MOSFET switch driven by GPIO to delay USB enume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
UART

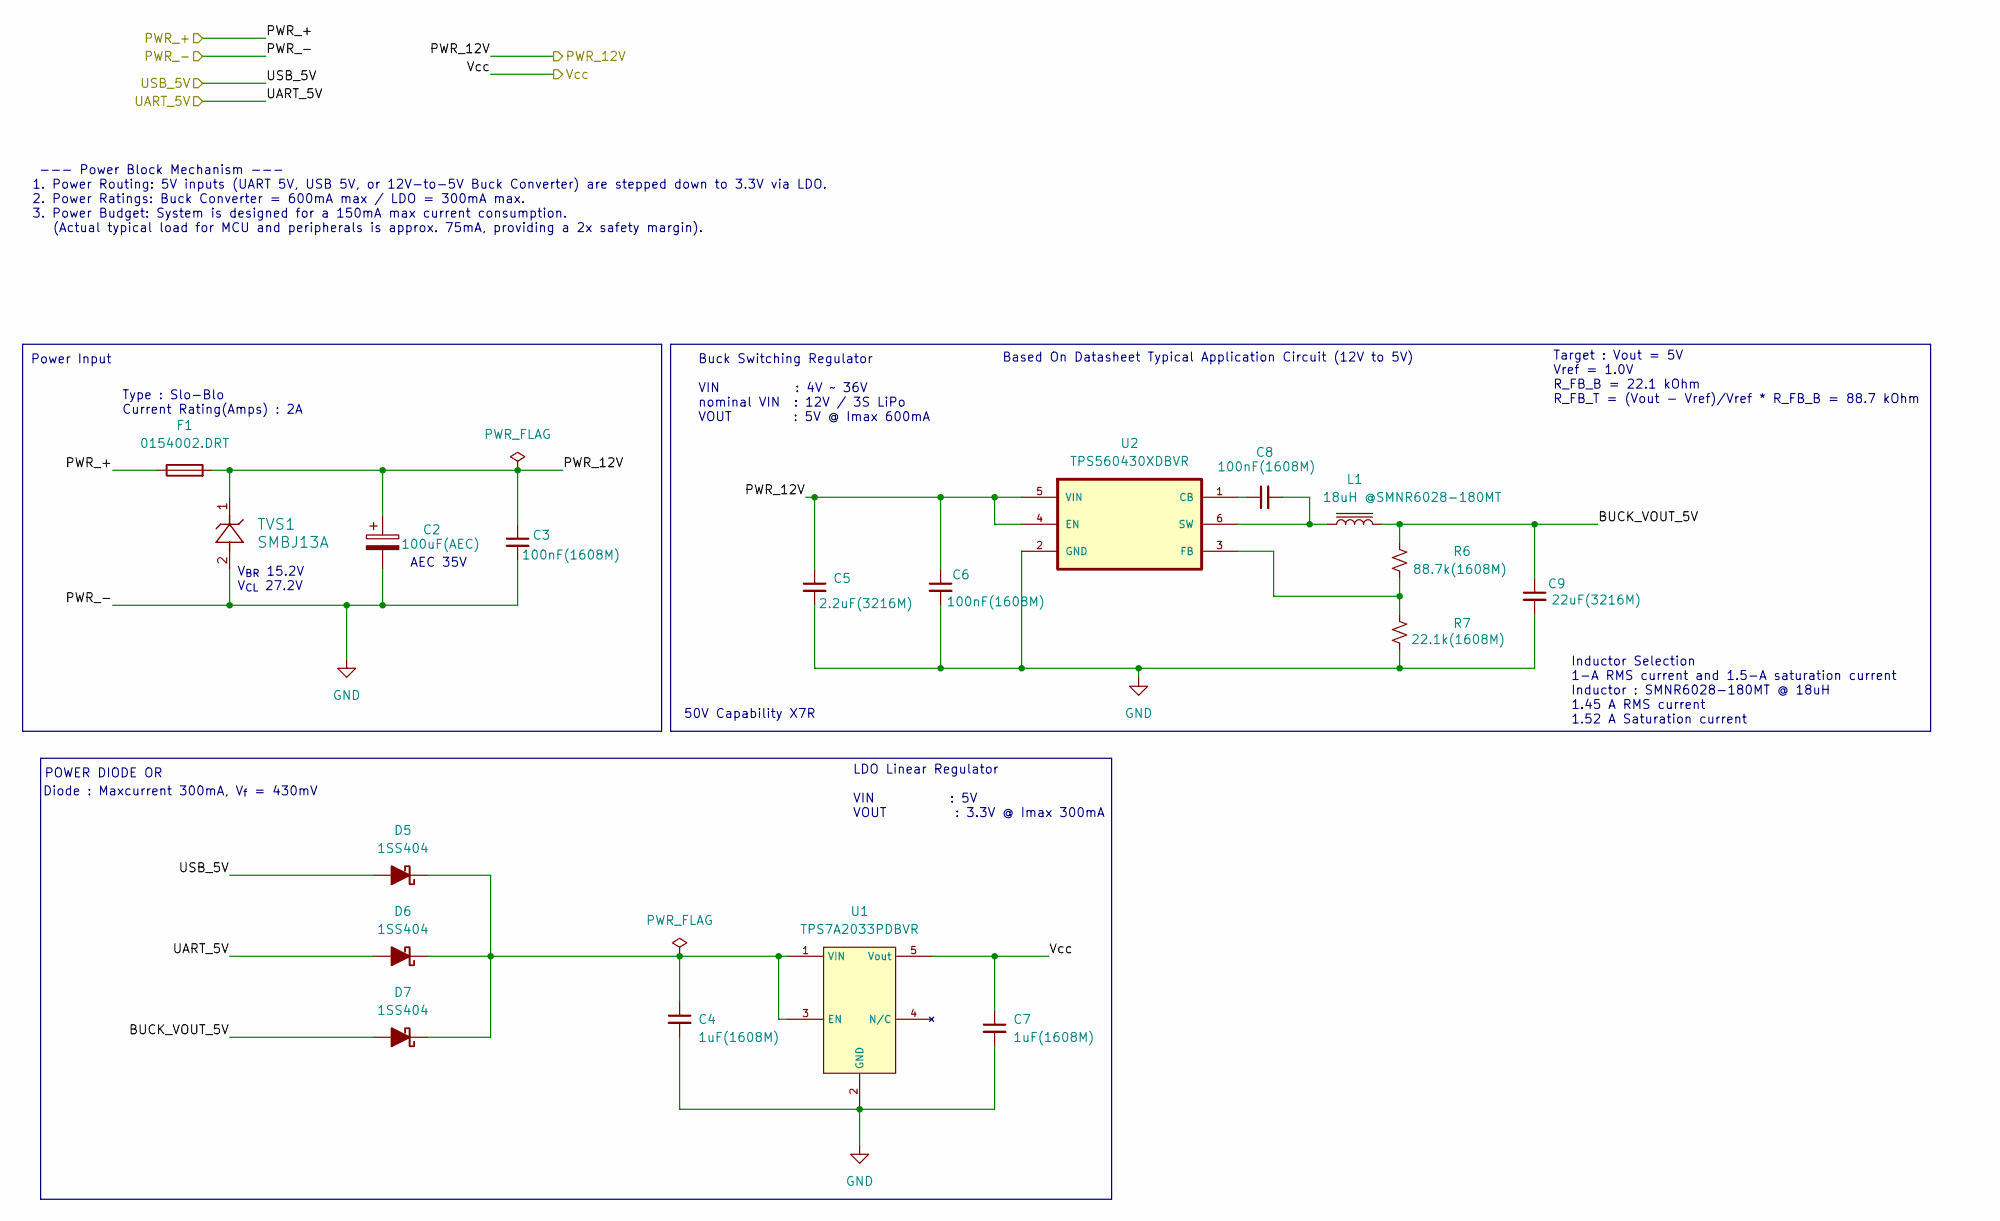
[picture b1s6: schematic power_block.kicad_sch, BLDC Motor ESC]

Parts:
C2: 100uF(AEC); CP_Elec_6.3x7.7; Part number RVT1V101M0607
C3, C6, C8: 100nF(1608M); C_0603_1608Metric; Part number GRM188R71H104KA93D
C4, C7: 1uF(1608M); C_0603_1608Metric; Part number CL10A105KA8NNNC
C5: 2.2uF(3216M); C_1206_3216Metric; Part number GRM31CR71H225KA88L
C9: 22uF(3216M); C_1206_3216Metric; Part number GRM31CR71A226KE15L
D5, D6, D7: 1SS404; D_SOD-323; Part number 1SS404
F1: 0154002.DRT; FUSE_154 Series OMNI-BLOK® Fuse and Holder Assembly; Part number 0154002.DRT
L1: 18uH @SMNR6028-180MT; Inductor SMNR6028-180MT; Part number SMNR6028-180MT
R6: 88.7k(1608M); R_0603_1608Metric; Part number 0603WAF8872T5E
R7: 22.1k(1608M); R_0603_1608Metric; Part number 0603WAF2212T5E
TVS1: SMBJ13A; TVS_Diode_SMD_SMB(DO-214AA); Part number SMBJ13A-TR
U1: TPS7A2033PDBVR; SOT-23-5; Part number TPS7A2033PDBVR
U2: TPS560430XDBVR; SOT-23-6(2.90 mm × 1.60 mm); Part number TPS560430XDBVR

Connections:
+3.3V: C7.1, U1.5 (Vout); also elsewhere on the board
+12V: C2.1, C3.1, C5.1, C6.1, F1.2, TVS1.1, U2.4 (EN), U2.5 (VIN); also elsewhere on the board
/POWER_BLOCK/BUCK_VOUT_5V: C9.1, D7.2 (A), L1.2, R6.2
/POWER_BLOCK/PWR_+: F1.1; also elsewhere on the board
/POWER_BLOCK/UART_5V: D6.2 (A); also elsewhere on the board
/POWER_BLOCK/USB_5V: D5.2 (A); also elsewhere on the board
GND: C2.2, C3.2, C4.2, C5.2, C6.2, C7.2, C9.2, R7.1, TVS1.2, U1.2 (GND), U2.2 (GND); also elsewhere on the board
unnamed: C4.1, D5.1 (K), D6.1 (K), D7.1 (K), U1.1 (VIN), U1.3 (EN)
unnamed: C8.1, U2.1 (CB)
unnamed: R6.1, R7.2, U2.3 (FB)
unnamed: C8.2, L1.1, U2.6 (SW)

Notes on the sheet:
Diode : Maxcurrent 300mA, V_{f} = 430mV
Based On Datasheet Typical Application Circuit (12V to 5V)
Target : Vout = 5V Vref = 1.0V R_FB_B = 22.1 kOhm R_FB_T = (Vout - Vref)/Vref * R_FB_B = 88.7 kOhm
Buck Switching Regulator VIN : 4V ~ 36V nominal VIN : 12V / 3S LiPo VOUT : 5V @ Imax 600mA
Inductor Selection 1-A RMS current and 1.5-A saturation current Inductor : SMNR6028-180MT @ 18uH 1.45 A RMS current 1.52 A Saturation current
50V Capability X7R
Type : Slo-Blo Current Rating(Amps) : 2A
Power Input
LDO Linear Regulator VIN : 5V VOUT : 3.3V @ Imax 300mA
POWER DIODE OR
--- Power Block Mechanism --- 1. Power Routing: 5V inputs (UART 5V, USB 5V, or 12V-to-5V Buck Converter) are stepped down to 3.3V via LDO. 2. Power Ratings: Buck Converter = 600mA max / LDO = 300mA max. 3. Power Budget: System is designed for a 150mA max current consumption. (Actual typical load fo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
AEC 35V
V_{BR} 15.2V V_{CL} 27.2V
